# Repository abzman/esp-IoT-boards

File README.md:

# esp8266-sensor-board

R5v: 1.9K for the red LED, 3.9K for the blue LED

Cfilter: 30pF
Rfilter: 4.7K

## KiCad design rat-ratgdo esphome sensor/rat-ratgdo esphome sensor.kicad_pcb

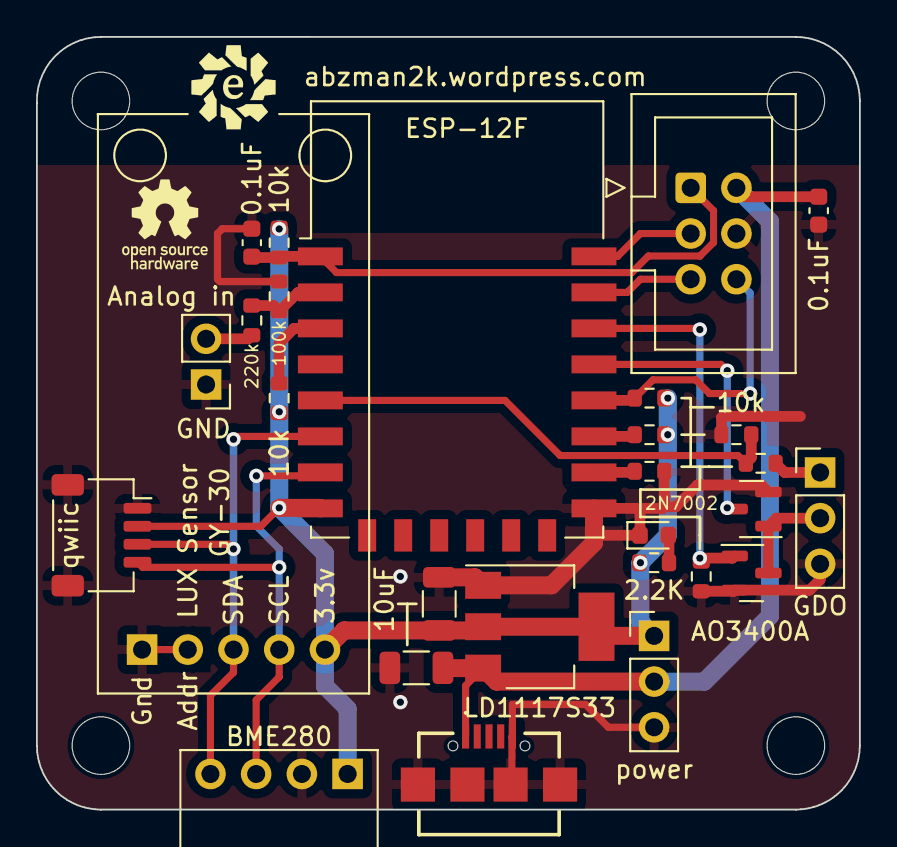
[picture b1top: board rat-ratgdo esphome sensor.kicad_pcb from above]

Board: 2 copper layers, 45.7 x 42.9 mm, 28 parts (0 on the bottom side), 20 nets.

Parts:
C1, C4: 0.1uF; C_0603_1608Metric
C2, C3: 10uF; C_1206_3216Metric
D1: RED LED; LED_0603_1608Metric
J1: Analog in; PinHeader_1x02_P2.54mm_Vertical
J2: Conn_02x03_Odd_Even; IDC-Header_2x03_P2.54mm_Vertical
J3: UJ2-MIBH-G-SMT-TR; UJ2MIBHGSMTTR
J4: LUX sensor
J6: bme280; BME280
J7: qwiic; JST_SH_SM04B-SRSS-TB_1x04-1MP_P1.00mm_Horizontal
J8: power; PinHeader_1x03_P2.54mm_Vertical
J9: GDO; PinHeader_1x03_P2.54mm_Vertical
Q1: 2N7002; SOT-23
Q2: AO3400A; SOT-23
R1, R2, R3, R6, R7, R8, R9, R11: 10k; R_0603_1608Metric
R4: 220k; R_0603_1608Metric
R5: 100k; R_0603_1608Metric
R10: 2.2K; R_0603_1608Metric
U1: LD1117S33; SOT-223-3_TabPin2
U2: ESP-12F; ESP-12E

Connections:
+3V3: C3.1, J4.5, J6.1, J7.2, J8.1, R3.1, R7.1, R8.1, R10.1, R11.1, U1.2 (VO), U2.8 (VCC)
+5V: C2.1, C4.1, J2.2, J3.1, J8.2, U1.3 (VI)
/Analog_In: J1.2, R4.1
/ESP_ADC: R4.2, R5.1, U2.2 (ADC)
/ESP_EN: R7.2, U2.3 (EN)
/ESP_IO0: J2.6, R11.2, U2.18 (GPIO0)
/ESP_IO1: J2.3, U2.22 (GPIO1/TXD)
/ESP_IO2: R8.2, U2.17 (GPIO2)
/ESP_IO3: J2.5, U2.21 (GPIO3/RXD)
/ESP_IO4: Q1.3 (D), U2.19 (GPIO4)
/ESP_IO5: Q2.1 (G), R9.1, U2.20 (GPIO5)
/ESP_IO12: J4.3, J6.4, J7.3, U2.6 (GPIO12)
/ESP_IO13: J4.4, J6.3, J7.4, U2.7 (GPIO13)
/ESP_IO14: R1.2, R2.1, U2.5 (GPIO14)
/ESP_IO15: R6.2, U2.16 (GPIO15)
/ESP_RST: C1.1, J2.1, R3.2, U2.1 (~RST)
/control_wire: J9.2, Q1.1 (G), Q2.3 (D)
/obstruction_sensor_wire: J9.1, R1.1
GND: C1.2, C2.2, C3.2, C4.2, D1.1 (K), J1.1, J2.4, J3.2, J3.MP1, J3.MP2, J3.MP3, J3.MP4, J4.1, J4.2, J6.2, J7.1, J7.MP, J8.3, J9.3, Q1.2 (S), Q2.2 (S), R2.2, R5.2, R6.1, R9.2, U1.1 (GND), U2.15 (GND)
unnamed: D1.2 (A), R10.2

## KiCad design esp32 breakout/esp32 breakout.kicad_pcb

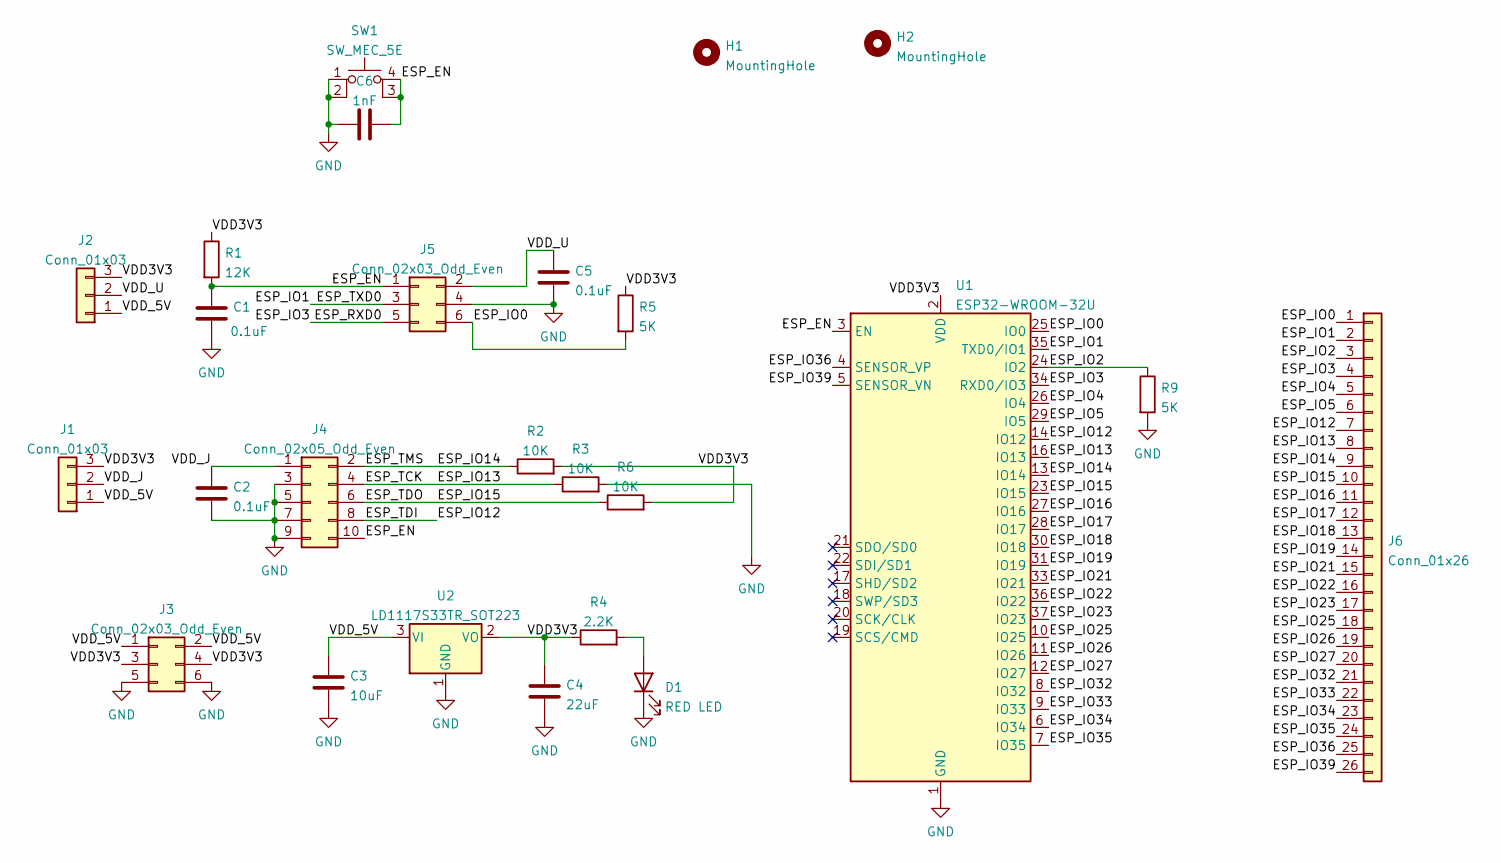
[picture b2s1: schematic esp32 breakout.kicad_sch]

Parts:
C1, C2, C5: 0.1uF; C_0603_1608Metric
C3: 10uF; CP_Radial_D5.0mm_P2.00mm
C4: 22uF; CP_Radial_D5.0mm_P2.00mm
C6: 1nF; C_0603_1608Metric
D1: RED LED; LED_0603_1608Metric
H1, H2: MountingHole; MountingHole_3.2mm_M3
J1, J2: Conn_01x03; PinHeader_1x03_P2.54mm_Vertical
J3: Conn_02x03_Odd_Even; PinHeader_2x03_P2.54mm_Vertical
J4: Conn_02x05_Odd_Even; IDC-Header_2x05_P2.54mm_Vertical
J5: Conn_02x03_Odd_Even; IDC-Header_2x03_P2.54mm_Vertical
J6: Conn_01x26; PinHeader_1x26_P2.54mm_Vertical
R1: 12K; R_0603_1608Metric
R2, R3, R6: 10K; R_0603_1608Metric
R4: 2.2K; R_0603_1608Metric
R5, R9: 5K; R_0603_1608Metric
SW1: SW_MEC_5E; SW_TH_Tactile_Omron_B3F-10xx
U1: ESP32-WROOM-32U
U2: LD1117S33TR_SOT223; SOT-223-3_TabPin2

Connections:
/ESP_EN: C1.1, C6.2, J4.10, J5.1, R1.2, SW1.3 (K), SW1.4 (A), U1.3 (EN)
/ESP_IO0: J5.6, J6.1, R5.2, U1.25 (IO0)
/ESP_IO1: J5.3, J6.2, U1.35 (TXD0/IO1)
/ESP_IO2: J6.3, R9.1, U1.24 (IO2)
/ESP_IO3: J5.5, J6.4, U1.34 (RXD0/IO3)
/ESP_IO4: J6.5, U1.26 (IO4)
/ESP_IO5: J6.6, U1.29 (IO5)
/ESP_IO12: J4.8, J6.7, U1.14 (IO12)
/ESP_IO13: J4.4, J6.8, R3.1, U1.16 (IO13)
/ESP_IO14: J4.2, J6.9, R2.1, U1.13 (IO14)
/ESP_IO15: J4.6, J6.10, R6.1, U1.23 (IO15)
/ESP_IO16: J6.11, U1.27 (IO16)
/ESP_IO17: J6.12, U1.28 (IO17)
/ESP_IO18: J6.13, U1.30 (IO18)
/ESP_IO19: J6.14, U1.31 (IO19)
/ESP_IO21: J6.15, U1.33 (IO21)
/ESP_IO22: J6.16, U1.36 (IO22)
/ESP_IO23: J6.17, U1.37 (IO23)
/ESP_IO25: J6.18, U1.10 (IO25)
/ESP_IO26: J6.19, U1.11 (IO26)
/ESP_IO27: J6.20, U1.12 (IO27)
/ESP_IO32: J6.21, U1.8 (IO32)
/ESP_IO33: J6.22, U1.9 (IO33)
/ESP_IO34: J6.23, U1.6 (IO34)
/ESP_IO35: J6.24, U1.7 (IO35)
/ESP_IO36: J6.25, U1.4 (SENSOR_VP)
/ESP_IO39: J6.26, U1.5 (SENSOR_VN)
/VDD3V3: C4.1, J1.3, J2.3, J3.3, J3.4, R1.1, R2.2, R4.1, R5.1, R6.2, U1.2 (VDD), U2.2 (VO)
/VDD_5V: C3.1, J1.1, J2.1, J3.1, J3.2, U2.3 (VI)
/VDD_J: C2.1, J1.2, J4.1
/VDD_U: C5.1, J2.2, J5.2
GND: C1.2, C2.2, C3.2, C4.2, C5.2, C6.1, D1.1 (K), J3.5, J3.6, J4.3, J4.5, J4.7, J4.9, J5.4, R3.2, R9.2, SW1.1, SW1.2, U1.1 (GND), U1.15 (GND), U1.38 (GND), U1.39 (GND), U2.1 (GND)
unnamed: D1.2 (A), R4.2

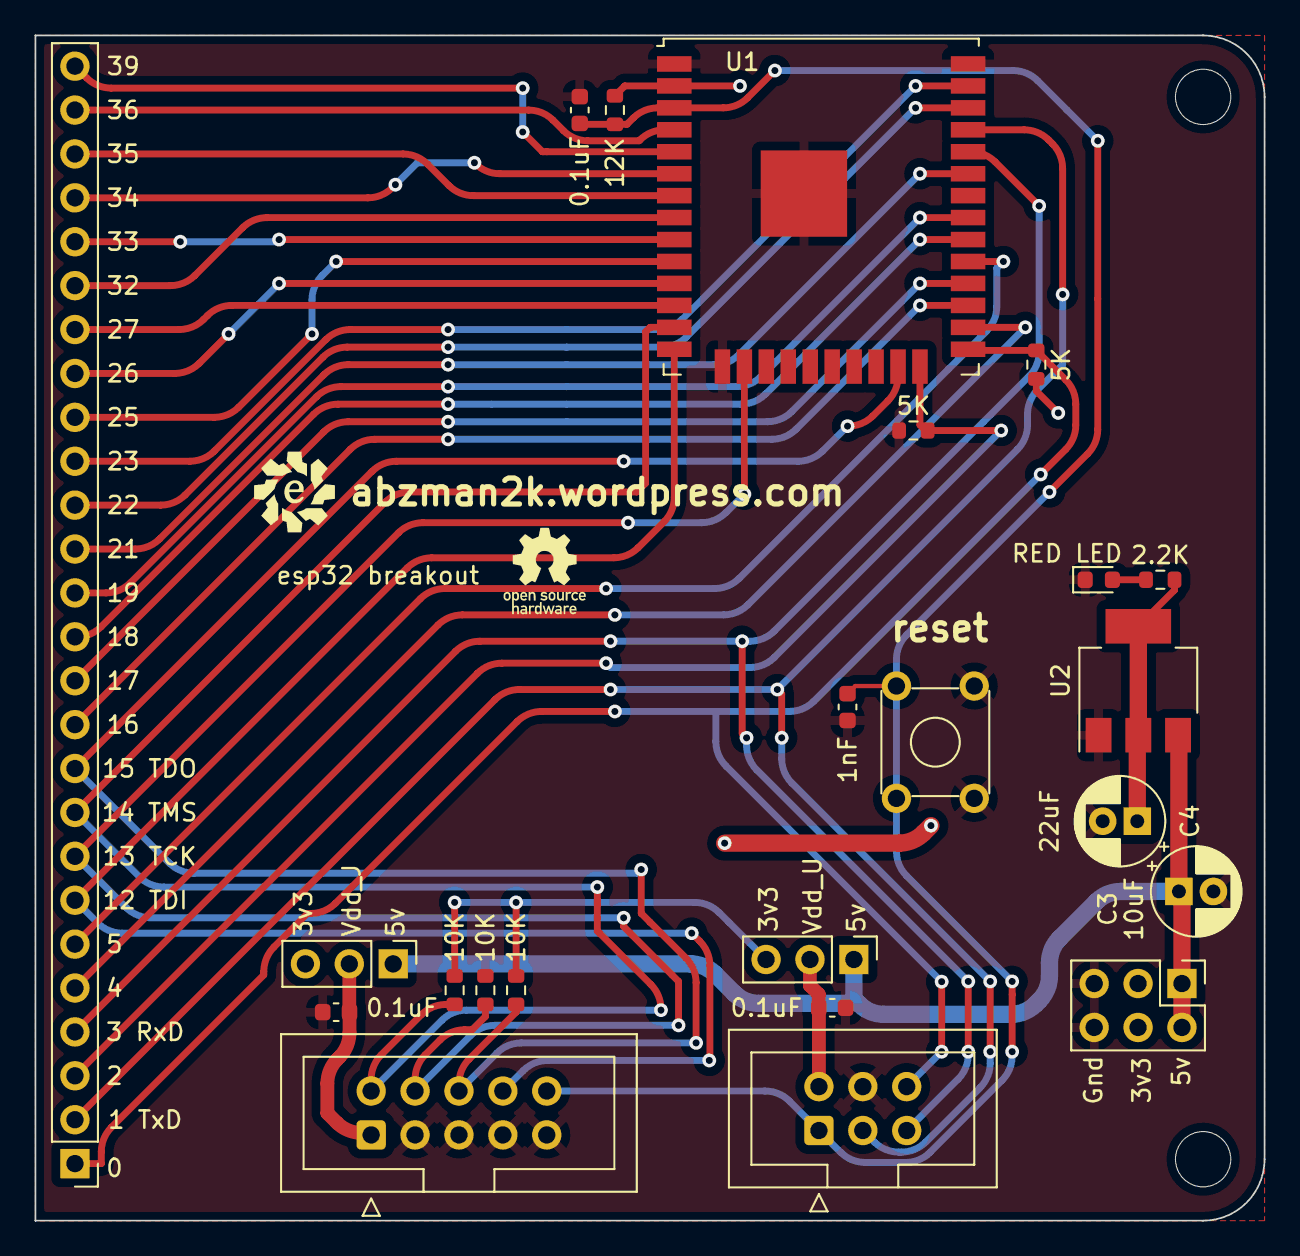
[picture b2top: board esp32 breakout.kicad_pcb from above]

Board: 2 copper layers, 71.1 x 68.6 mm, 25 parts (0 on the bottom side), 33 nets.

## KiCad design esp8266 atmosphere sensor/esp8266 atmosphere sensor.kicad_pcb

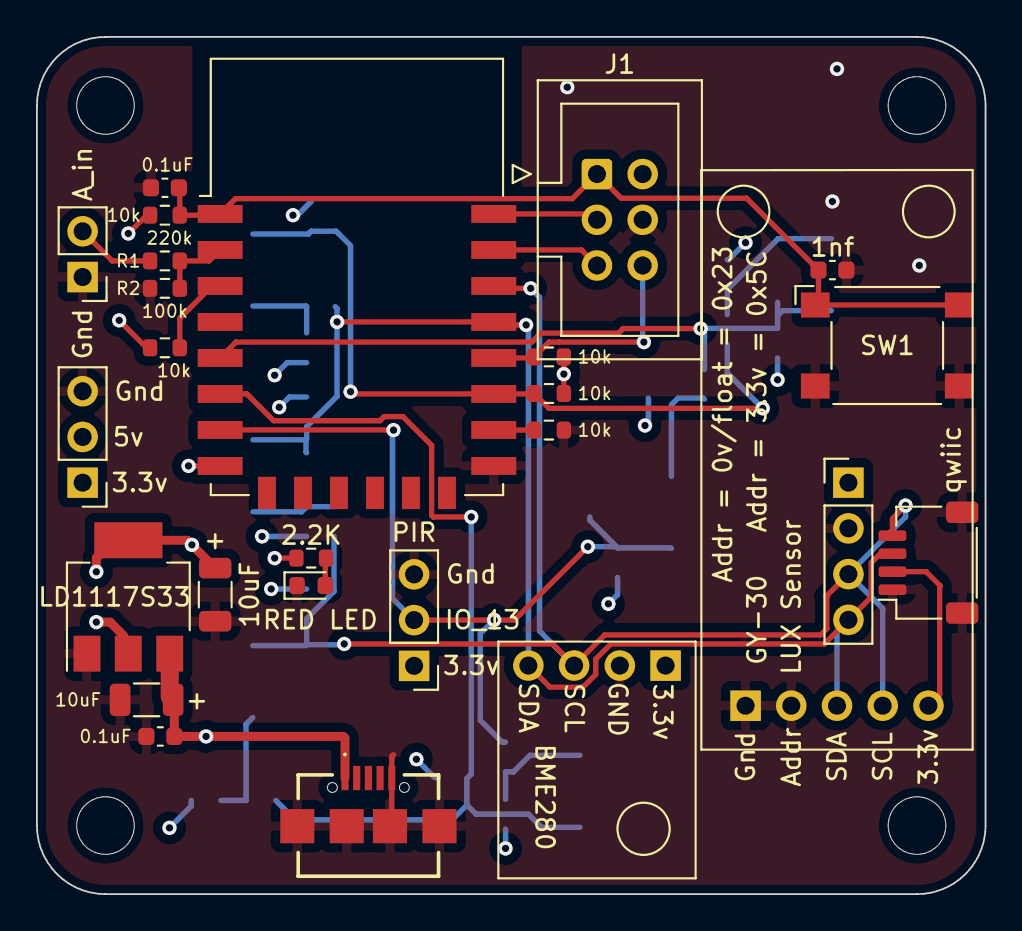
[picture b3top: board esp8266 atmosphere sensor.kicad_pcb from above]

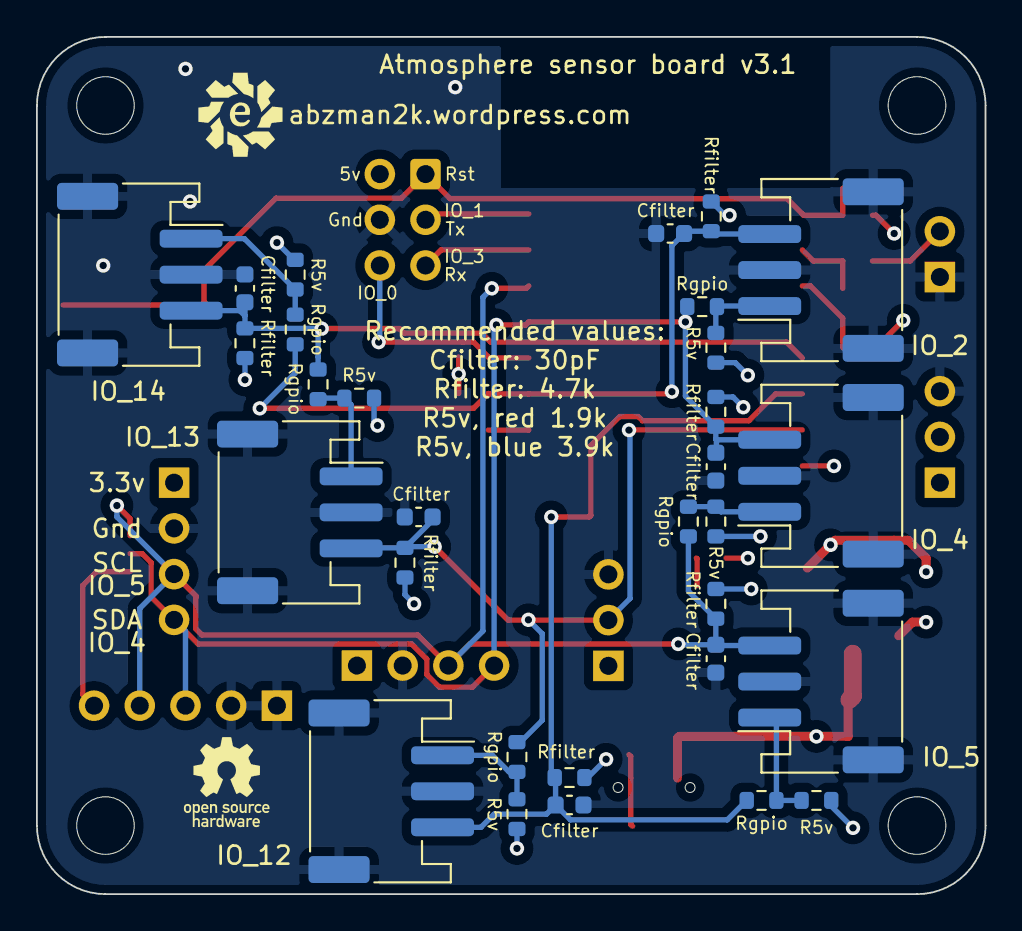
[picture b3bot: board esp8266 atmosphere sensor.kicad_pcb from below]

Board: 4 copper layers, 52.7 x 47.6 mm, 56 parts (30 on the bottom side), 24 nets.

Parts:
C1, C3: 10uF; C_1206_3216Metric
C2, C9: 0.1uF; C_0603_1608Metric
C4: 1nf; C_0603_1608Metric
C5, C6, C7, C8, C10, C11: Cfilter; C_0603_1608Metric
D1: RED LED; LED_0603_1608Metric
J1: Conn_02x03_Odd_Even; IDC-Header_2x03_P2.54mm_Vertical
J2: UJ2-MIBH-G-SMT-TR; UJ2MIBHGSMTTR
J3: LUX sensor
J4: bme280; BME280
J5: PIR; PinHeader_1x03_P2.54mm_Vertical
J6: Analog in; PinHeader_1x02_P2.54mm_Vertical
J7: external i2c; PinHeader_1x04_P2.54mm_Vertical
J8: power; PinHeader_1x03_P2.54mm_Vertical
J9, J10, J11, J12, J13, J14: Conn_01x03; JST_PH_S3B-PH-SM4-TB_1x03-1MP_P2.00mm_Horizontal
J15: qwiic; JST_SH_SM04B-SRSS-TB_1x04-1MP_P1.00mm_Horizontal
R1: 220k; R_0603_1608Metric
R2: 100k; R_0603_1608Metric
R3: 2.2K; R_0603_1608Metric
R4, R12, R15, R18, R21, R24: R5v; R_0603_1608Metric
R5, R8, R9, R10, R11: 10k; R_0603_1608Metric
R6, R13, R16, R19, R22, R25: Rgpio; R_0603_1608Metric
R7, R14, R17, R20, R23, R26: Rfilter; R_0603_1608Metric
SW1: SW_MEC_5E; SW_SPST_Omron_B3FS-105xP
U1: ESP-12F; ESP-12E
U2: LD1117S33; SOT-223-3_TabPin2

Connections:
+3V3: C1.1, J3.5, J4.1, J5.1, J7.1, J8.1, J15.2, R3.1, R7.1, R8.1, R9.1, R10.1, R11.1, R14.1, R17.1, R20.1, R23.1, R26.1, U1.8 (VCC), U2.2 (VO)
+5V: C2.1, C3.1, J1.2, J2.1, J8.2, R4.1, R12.1, R15.1, R18.1, R21.1, R24.1, U2.3 (VI)
/Analog_In: J6.2, R1.1
/ESP_ADC: R1.2, R2.1, U1.2 (ADC)
/ESP_EN: R8.2, U1.3 (EN)
/ESP_IO0: J1.6, R10.2, U1.18 (GPIO0)
/ESP_IO1: J1.3, U1.22 (GPIO1/TXD)
/ESP_IO2: C5.1, J9.3, R7.2, R11.2, R22.2, U1.17 (GPIO2)
/ESP_IO3: J1.5, U1.21 (GPIO3/RXD)
/ESP_IO4: C11.1, J3.3, J4.4, J7.4, J14.3, J15.3, R6.2, R26.2, U1.19 (GPIO4)
/ESP_IO5: C6.1, J3.4, J4.3, J7.3, J10.3, J15.4, R14.2, R25.2, U1.20 (GPIO5)
/ESP_IO12: C7.1, J11.3, R13.2, R17.2, U1.6 (GPIO12)
/ESP_IO13: C8.1, J5.2, J12.3, R16.2, R20.2, U1.7 (GPIO13)
/ESP_IO14: C10.1, J13.3, R19.2, R23.2, U1.5 (GPIO14)
/ESP_IO15: R5.2, U1.16 (GPIO15)
/ESP_RST: C4.1, C9.1, J1.1, R9.2, SW1.1, SW1.2, U1.1 (~RST)
GND: C1.2, C2.2, C3.2, C4.2, C5.2, C6.2, C7.2, C8.2, C9.2, C10.2, C11.2, D1.1 (K), J1.4, J2.2, J2.MP1, J2.MP2, J2.MP3, J2.MP4, J3.1, J3.2, J4.2, J5.3, J6.1, J7.2, J8.3, J9.2, J9.MP, J10.2, J10.MP, J11.2, J11.MP, J12.2, J12.MP, J13.2, J13.MP, J14.2, J14.MP, J15.1, J15.MP, R2.2, R5.1, SW1.3 (K), SW1.4 (A), U1.15 (GND), U2.1 (GND)
unnamed: D1.2 (A), R3.2
unnamed: J9.1, R4.2, R6.1
unnamed: J10.1, R12.2, R13.1
unnamed: J11.1, R15.2, R16.1
unnamed: J12.1, R18.2, R19.1
unnamed: J13.1, R21.2, R22.1
unnamed: J14.1, R24.2, R25.1

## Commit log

2022-02-09 atmosphere sensor laid out
2022-02-09 added extra i2c and filtered buttons
2022-03-14 gerber zip
2022-10-16 updated footprints
2022-10-17 redid layout as 4-layer without moving parts
2022-11-25 generated gerbers, added gitignore
2022-11-26 added notes for populating switch components
2022-12-27 tweaked silk for proper labels
2022-12-31 tweaked locations for button connectors
2022-12-31 new gerbers for v3.1
2023-11-03 moved 2 more esp8266 boards from other repo
    https://github.com/abzman/small-useful-PCBs
2023-11-03 brought in big esp32 board from fujinet repo
    https://github.com/abzman/fujinet-things
2023-11-03 added board from thermostat project
    https://github.com/abzman/basic-esp32-thermostat
2023-12-13 finished initial design for esphome ratgdo board
2023-12-22 added bottom mount
2024-01-16 ratgdo gerbers
2024-01-16 atmosphere sensor brackets
2024-01-16 remove redundant parts
2024-02-09 added bracket
2024-02-10 ratgdo brackets
2024-02-10 revisions for design error
2024-07-28 revised and added 3d models for enclosures
